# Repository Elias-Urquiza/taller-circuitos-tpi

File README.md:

# Proyecto Integrador del Taller de Circuitos Electrónicos

TP de tomi,nacho,elias y vero.

## 🐥 Git Branching: Guía Rápida con Panchito el Pollito 🐥

¡Hola, ameo! Soy Panchito, el pollito piola fui creado por IA para hacer más copado el usar Git 🐥, y te voy a guiar paso a paso para que aprendas cómo usar ramas (branches) en Git. Tranquilo, que lo hacemos simple y sin vueltas. ¡Vamo a meterle! 💪

---

## ¿Qué es una rama (branch)? 🌿

Bueno, imaginate que estás laburando en tu proyecto y querés probar algo nuevo sin que se rompa lo que ya tenés hecho. Ahí es donde entran las **ramas**. 🌱 Cada rama es como una copia separada del proyecto en la que podés hacer lío sin romper nada. Cuando ya esté todo pipí cucú, unís los cambios al proyecto principal y listo. 🎉

---

## Comandos Básicos para Trabajar con Ramas 🐾

### 1. Verificar en qué rama estás 🔍

Primero lo primero, ¿en qué rama estás? Para saberlo, usá este comando:

```bash
git branch
```

Te va a mostrar todas las ramas y te pone un asterisco `*` al lado de la que tenés activa. ¡Así sabés bien en qué andás! 💡

### 2. Crear una nueva rama 🌱

Cuando quieras hacer algo nuevo, lo mejor es crear una rama aparte (esto lo vamos a hacer todos una vez sola). Mandá este comando:

```bash
git branch pruebas_pepe
```

Este comando te crea la nueva rama, pero ¡ojo! todavía no te moviste a ella. Ahora vamos a eso. 🐥

### 3. Cambiar a una nueva rama 🎯

Para empezar a trabajar en la nueva rama, usá el siguiente comando:

```bash
git checkout pruebas_pepe
```

¡Listo! Ya estás en la nueva rama y podés hacer todos los cambios que quieras sin afectar el resto del proyecto. 🚀

### 4. Crear y cambiar a una nueva rama al mismo tiempo ⚡

Si te da fiaca hacer dos pasos, podés crear y cambiar a la nueva rama de una:

```bash
git checkout -b pruebas_pepe
```

Así no perdés tiempo y ya te ponés a laburar directo, como Panchito corriendo de acá para allá. 🐤

### 5. Verificar que estás en la nueva rama 🦅

Para asegurarte de que estás en la rama correcta, tirá de nuevo:

```bash
git branch
```

Ahí vas a ver el asterisco `*` al lado de la rama en la que estás. ¡Pío pío, ya estás listo para seguir! 🐥

### 6. Subir la nueva rama al repositorio remoto 🌍

Si querés compartir tus cambios con otros o simplemente guardar la rama en un repositorio remoto (como GitHub), tenés que hacer esto:

```bash
git push origin pruebas_pepe
```

Así, todo el mundo puede ver lo que hiciste y meter mano si hace falta. ¡No te olvides de esto cuando termines! 😉

### 7. Cambiar a una rama existente y subirla

1. **Cambiar a una rama existente:**
   ```bash
   git checkout nombre-de-la-rama
   ```

2. **Subir la rama al repositorio remoto si aún no está allí:**
   ```bash
   git push origin nombre-de-la-rama
   ```

### 8. Sincronizar una rama con `origin`

1. **Obtener los cambios del repositorio remoto:**
   ```bash
   git fetch origin
   ```

2. **Fusionar los cambios del repositorio remoto con tu rama local:**
   ```bash
   git merge origin/nombre-de-la-rama
   ```

   O, para actualizar tu rama local con los cambios remotos sin hacer un merge, puedes usar:
   ```bash
   git pull origin nombre-de-la-rama
   ```

### 9. Eliminar una rama en `origin`

1. **Eliminar una rama remota:**
   ```bash
   git push origin --delete nombre-de-la-rama
   ```

### 10. Ver ramas en `origin`

1. **Ver todas las ramas remotas:**
   ```bash
   git branch -r
   ```

2. **Ver todas las ramas locales y remotas:**
   ```bash
   git branch -a
   ```

### 11. Configurar el "upstream" de la rama

Si ves un mensaje que te indica que la rama no tiene un "upstream" configurado, usá este comando para empujar la rama y, al mismo tiempo, configurarla para que se conecte automáticamente con el repositorio remoto en futuras ocasiones:

```bash
git push --set-upstream origin nombre-de-la-rama
```

### ¿Qué hace este comando?

1. `git push`: Empuja los cambios al repositorio remoto.
2. `--set-upstream`: Configura la rama actual para que se conecte con la rama del mismo nombre en el repositorio remoto (en tu caso, `origin`).
3. `origin nombre-de-la-rama`: Le dice a Git que esta rama debe asociarse con la rama del mismo nombre en el repositorio remoto `origin`.

De ahora en más, cuando estés en la rama `nombre-de-la-rama`, podés usar simplemente `git push` sin tener que configurar el upstream de nuevo. ¡Listo!

---

## ¡Panchito dice: A practicar! 🐥🚀

Ahora que sabés cómo usar las ramas, ¡es hora de que te pongas a practicar! No tengas miedo de probar cosas nuevas. 
Git te cuida las espaldas, así que si algo no sale como esperabas, podés volver atrás sin problemas. ¡Vamos que se puede! 💪🐥🎉

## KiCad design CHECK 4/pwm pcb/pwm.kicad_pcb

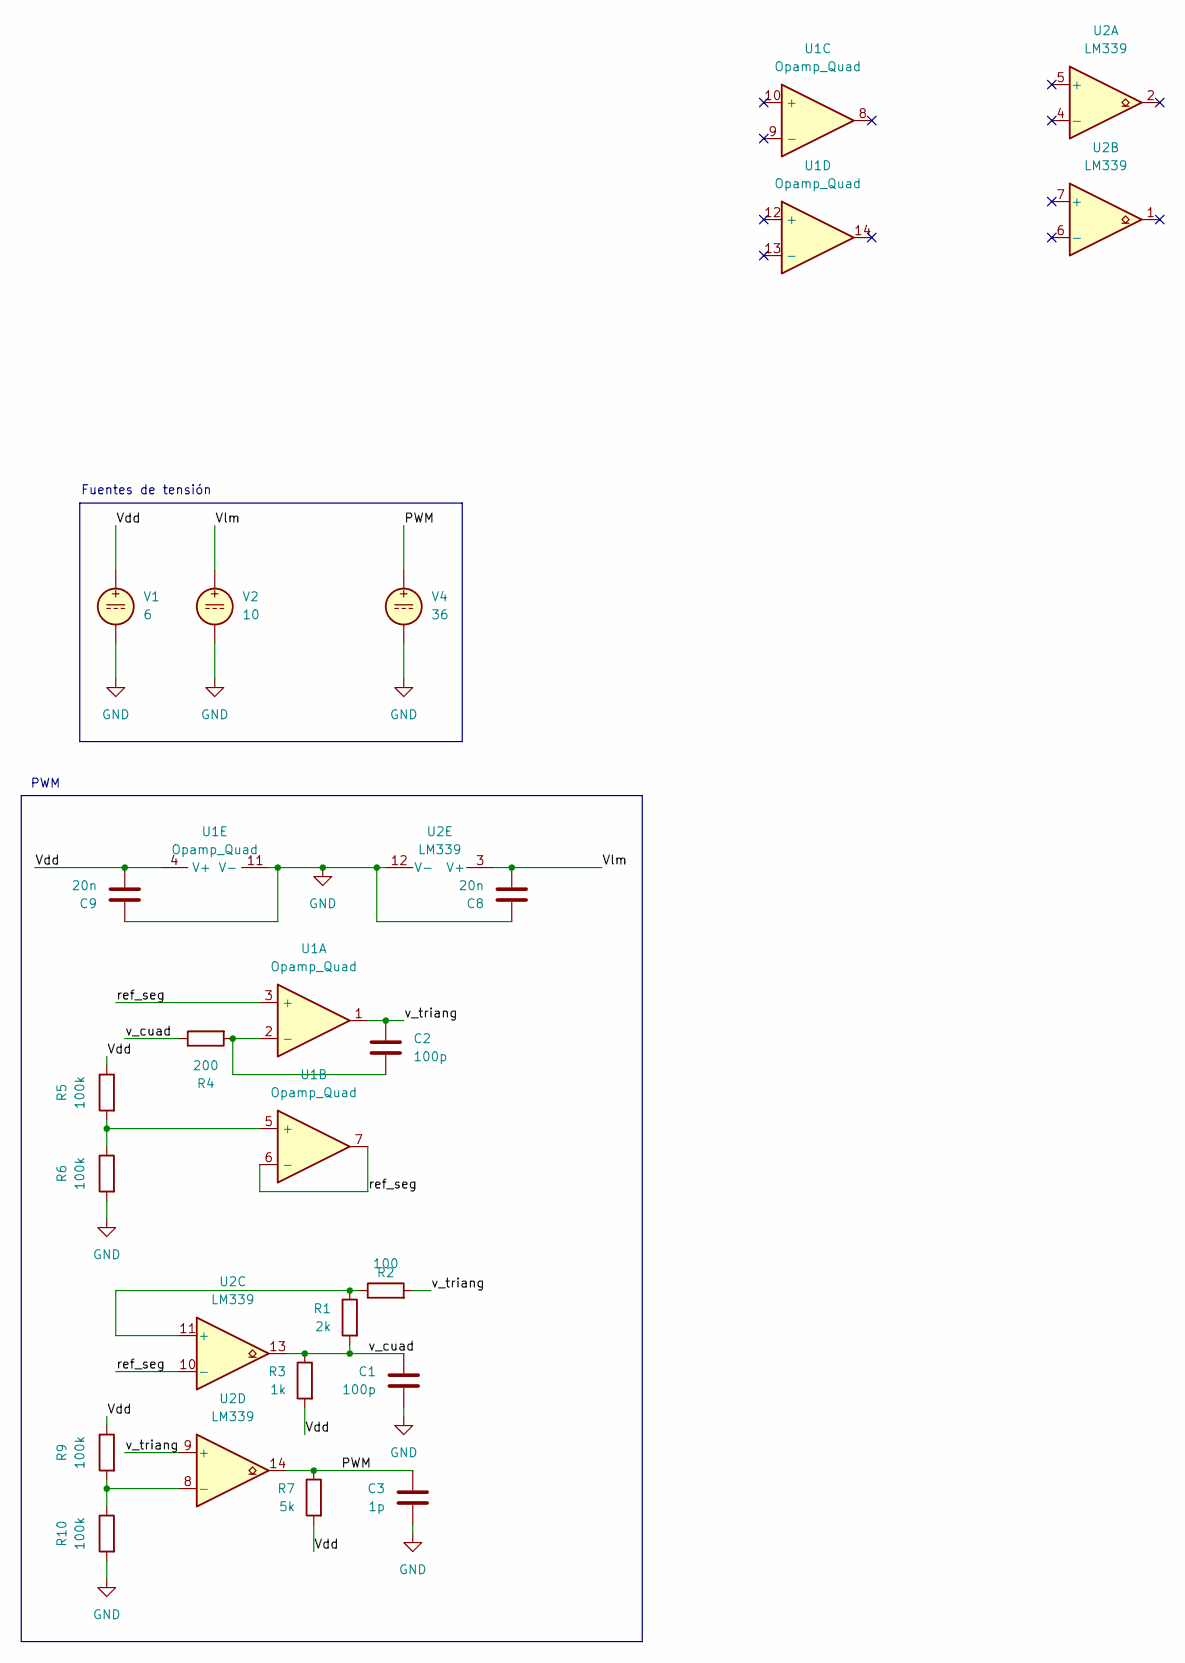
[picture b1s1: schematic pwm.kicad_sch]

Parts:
C1, C2: 100p; C_2225_5664Metric_Pad1.80x6.60mm_HandSolder
C3: 1p; C_2225_5664Metric_Pad1.80x6.60mm_HandSolder
C8, C9: 20n; C_2225_5664Metric_Pad1.80x6.60mm_HandSolder
R1: 2k; R_2512_6332Metric_Pad1.40x3.35mm_HandSolder
R2: 100; R_2512_6332Metric_Pad1.40x3.35mm_HandSolder
R3: 1k; R_2512_6332Metric_Pad1.40x3.35mm_HandSolder
R4: 200; R_2512_6332Metric_Pad1.40x3.35mm_HandSolder
R5, R6, R9, R10: 100k; R_2512_6332Metric_Pad1.40x3.35mm_HandSolder
R7: 5k; R_2512_6332Metric_Pad1.40x3.35mm_HandSolder
U1: Opamp_Quad; DIP-14_W10.16mm_LongPads
U2: LM339; DIP-14_W10.16mm_LongPads
V1: 6; PinHeader_2x01_P2.54mm_Vertical
V2: 10; PinHeader_2x01_P2.54mm_Vertical
V4: 36; PinHeader_2x01_P2.54mm_Vertical

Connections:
/PWM: C3.1, R7.1, U2.14, V4.1
/Vdd: C9.2, R3.2, R5.1, R7.2, R9.1, U1.4 (V+), V1.1
/Vlm: C8.2, U2.3 (V+), V2.1
/ref_seg: U1.3 (+), U1.6 (-), U1.7, U2.10 (-)
/v_cuad: C1.1, R1.2, R3.1, R4.1, U2.13
/v_triang: C2.1, R2.2, U1.1, U2.9 (+)
GND: C1.2, C3.2, C8.1, C9.1, R6.2, R10.2, U1.11 (V-), U2.12 (V-), V1.2, V2.2, V4.2
unnamed: C2.2, R4.2, U1.2 (-)
unnamed: R5.2, R6.1, U1.5 (+)
unnamed: R1.1, R2.1, U2.11 (+)
unnamed: R9.2, R10.1, U2.8 (-)

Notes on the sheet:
PWM
Fuentes de tensión

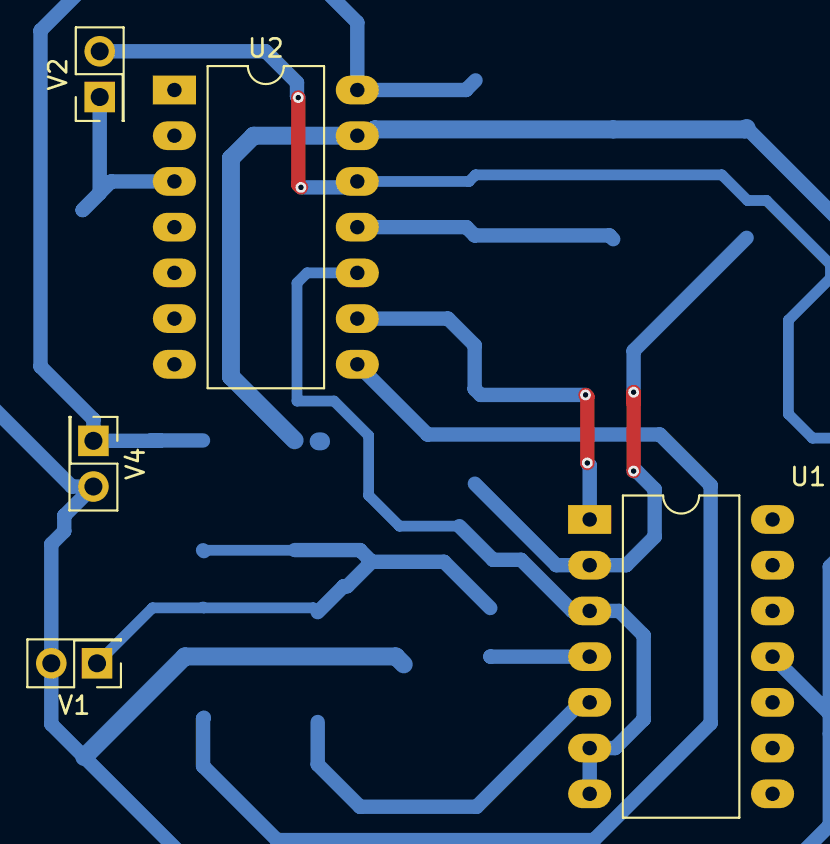
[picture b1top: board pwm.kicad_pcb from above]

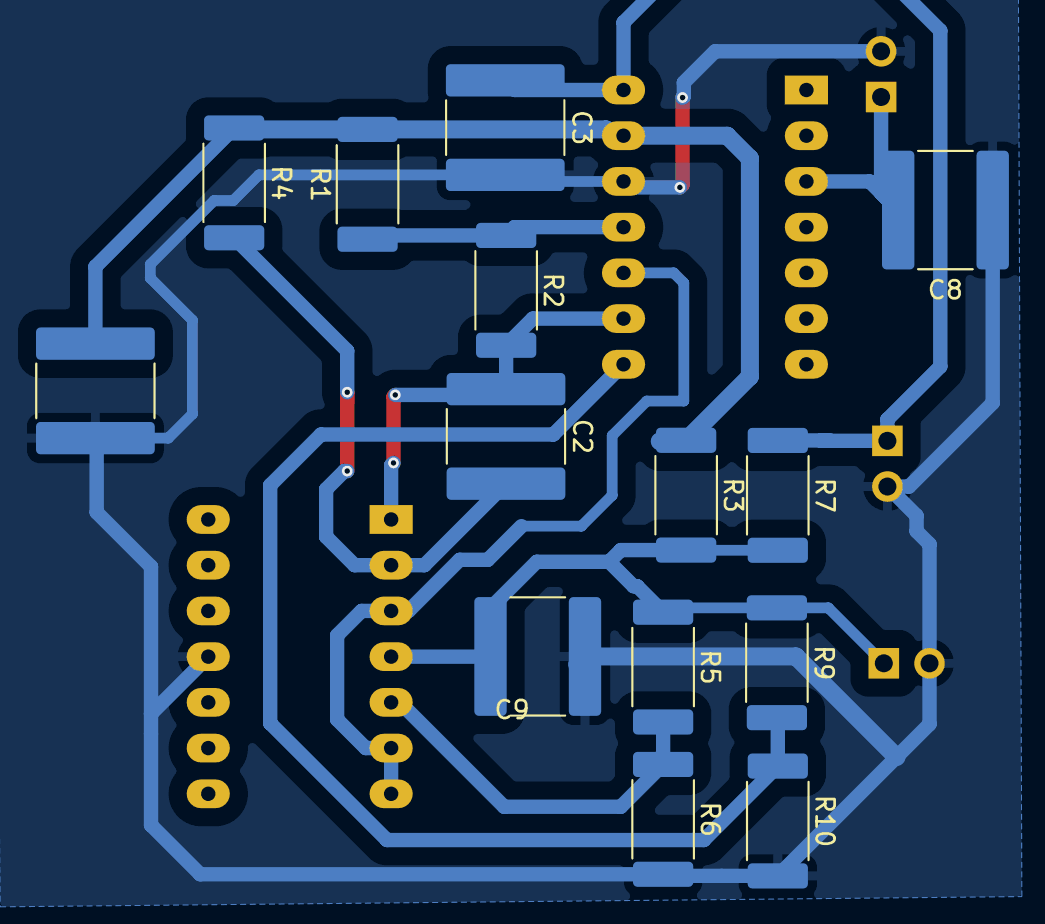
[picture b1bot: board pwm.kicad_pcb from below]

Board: 2 copper layers, 19 parts (14 on the bottom side), 11 nets.

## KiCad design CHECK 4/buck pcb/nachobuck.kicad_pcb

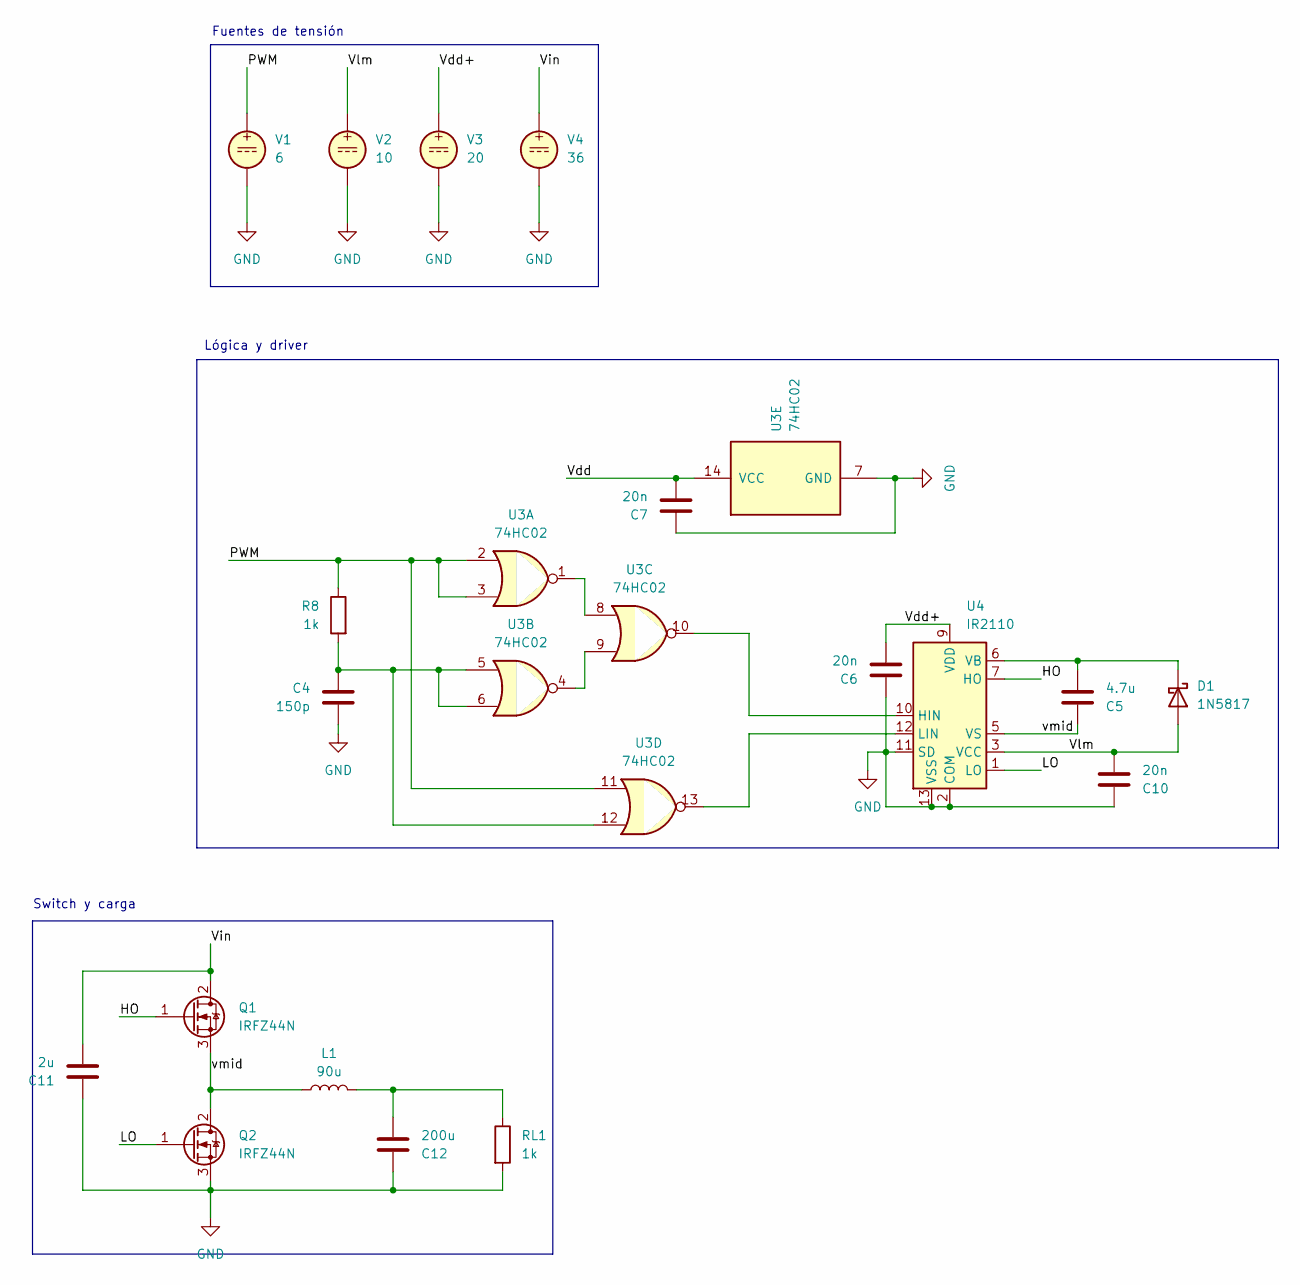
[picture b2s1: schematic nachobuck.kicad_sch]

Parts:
C4: 150p; C_2225_5664Metric_Pad1.80x6.60mm_HandSolder
C5: 4.7u; C_2225_5664Metric_Pad1.80x6.60mm_HandSolder
C6, C7, C10: 20n; C_2225_5664Metric_Pad1.80x6.60mm_HandSolder
C11: 2u; C_2225_5664Metric_Pad1.80x6.60mm_HandSolder
C12: 200u; C_2225_5664Metric_Pad1.80x6.60mm_HandSolder
D1: 1N5817; D_DO-41_SOD81_P10.16mm_Horizontal
L1: 90u; L_Axial_L30.0mm_D8.0mm_P35.56mm_Horizontal_Fastron_77A
Q1, Q2: IRFZ44N; TO-220-3_Vertical
R8: 1k; R_2512_6332Metric_Pad1.40x3.35mm_HandSolder
RL1: 1k; PinHeader_2x01_P2.54mm_Vertical
U3: 74HC02; DIP-14_W10.16mm_LongPads
U4: IR2110; DIP-14_W7.62mm
V1: 6; PinHeader_2x01_P2.54mm_Vertical
V2: 10; PinHeader_2x01_P2.54mm_Vertical
V3: 20; PinHeader_2x01_P2.54mm_Vertical
V4: 36; PinHeader_2x01_P2.54mm_Vertical

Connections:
/HO: Q1.1 (G), U4.7 (HO)
/LO: Q2.1 (G), U4.1 (LO)
/PWM: R8.1, U3.2, U3.3, U3.11, V1.1
/Vdd: C7.2, U3.14 (VCC)
/Vdd+: C6.2, U4.9 (VDD), V3.1
/Vin: C11.2, Q1.2 (D), V4.1
/Vlm: C10.2, D1.2 (A), U4.3 (VCC), V2.1
/vmid: C5.1, L1.1, Q1.3 (S), Q2.2 (D), U4.5 (VS)
GND: C4.2, C6.1, C7.1, C10.1, C11.1, C12.1, Q2.3 (S), RL1.2, U3.7 (GND), U4.2 (COM), U4.11 (SD), U4.13 (VSS), V1.2, V2.2, V3.2, V4.2
unnamed: C4.1, R8.2, U3.5, U3.6, U3.12
unnamed: C12.2, L1.2, RL1.1
unnamed: C5.2, D1.1 (K), U4.6 (VB)
unnamed: U3.1, U3.8
unnamed: U3.4, U3.9
unnamed: U3.10, U4.10 (HIN)
unnamed: U3.13, U4.12 (LIN)

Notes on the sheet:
Fuentes de tensión
Switch y carga
Lógica y driver

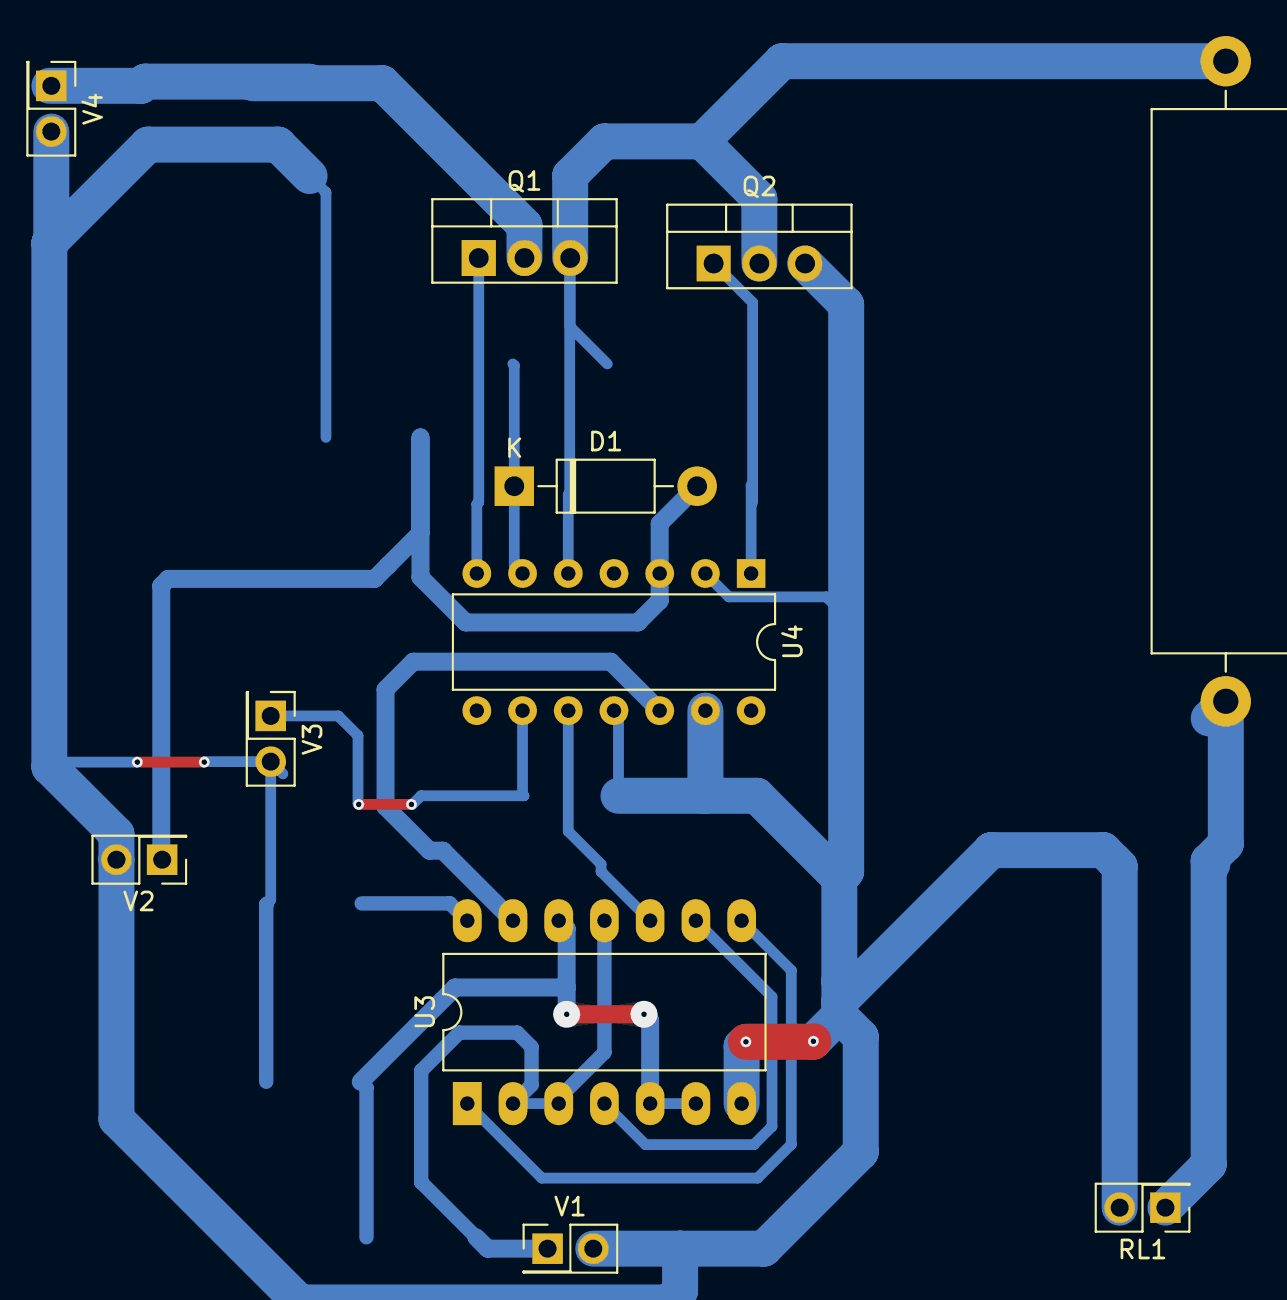
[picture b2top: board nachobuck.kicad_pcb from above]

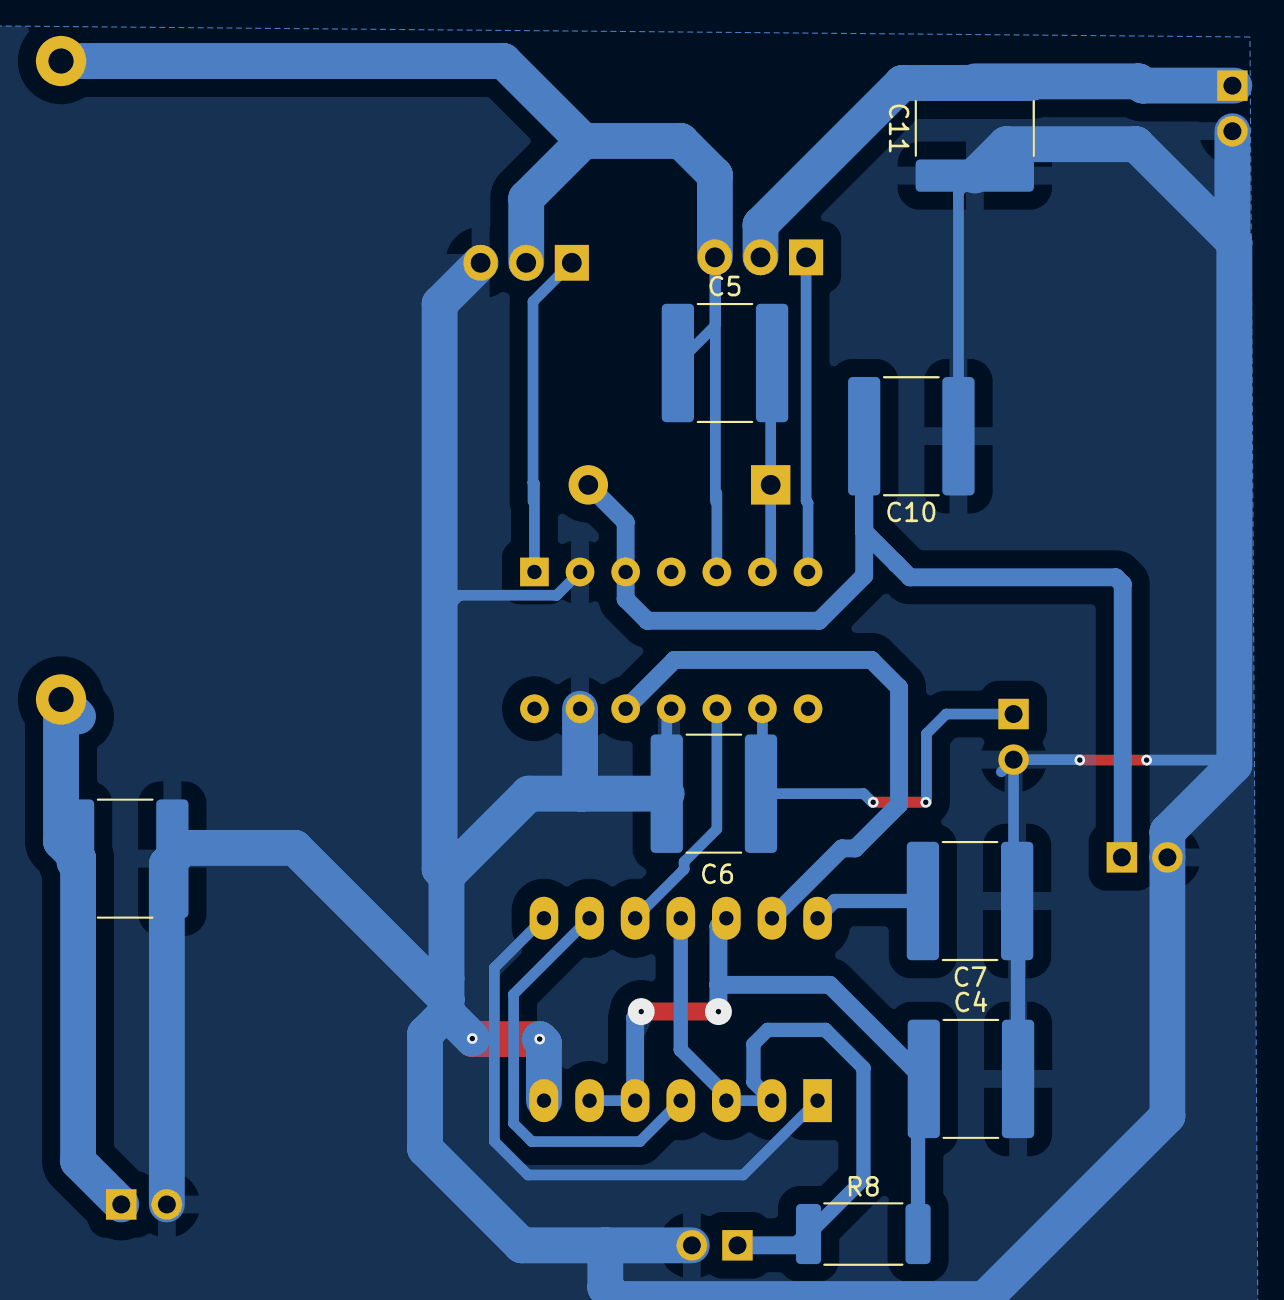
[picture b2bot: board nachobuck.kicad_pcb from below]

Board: 2 copper layers, 19 parts (8 on the bottom side), 16 nets.

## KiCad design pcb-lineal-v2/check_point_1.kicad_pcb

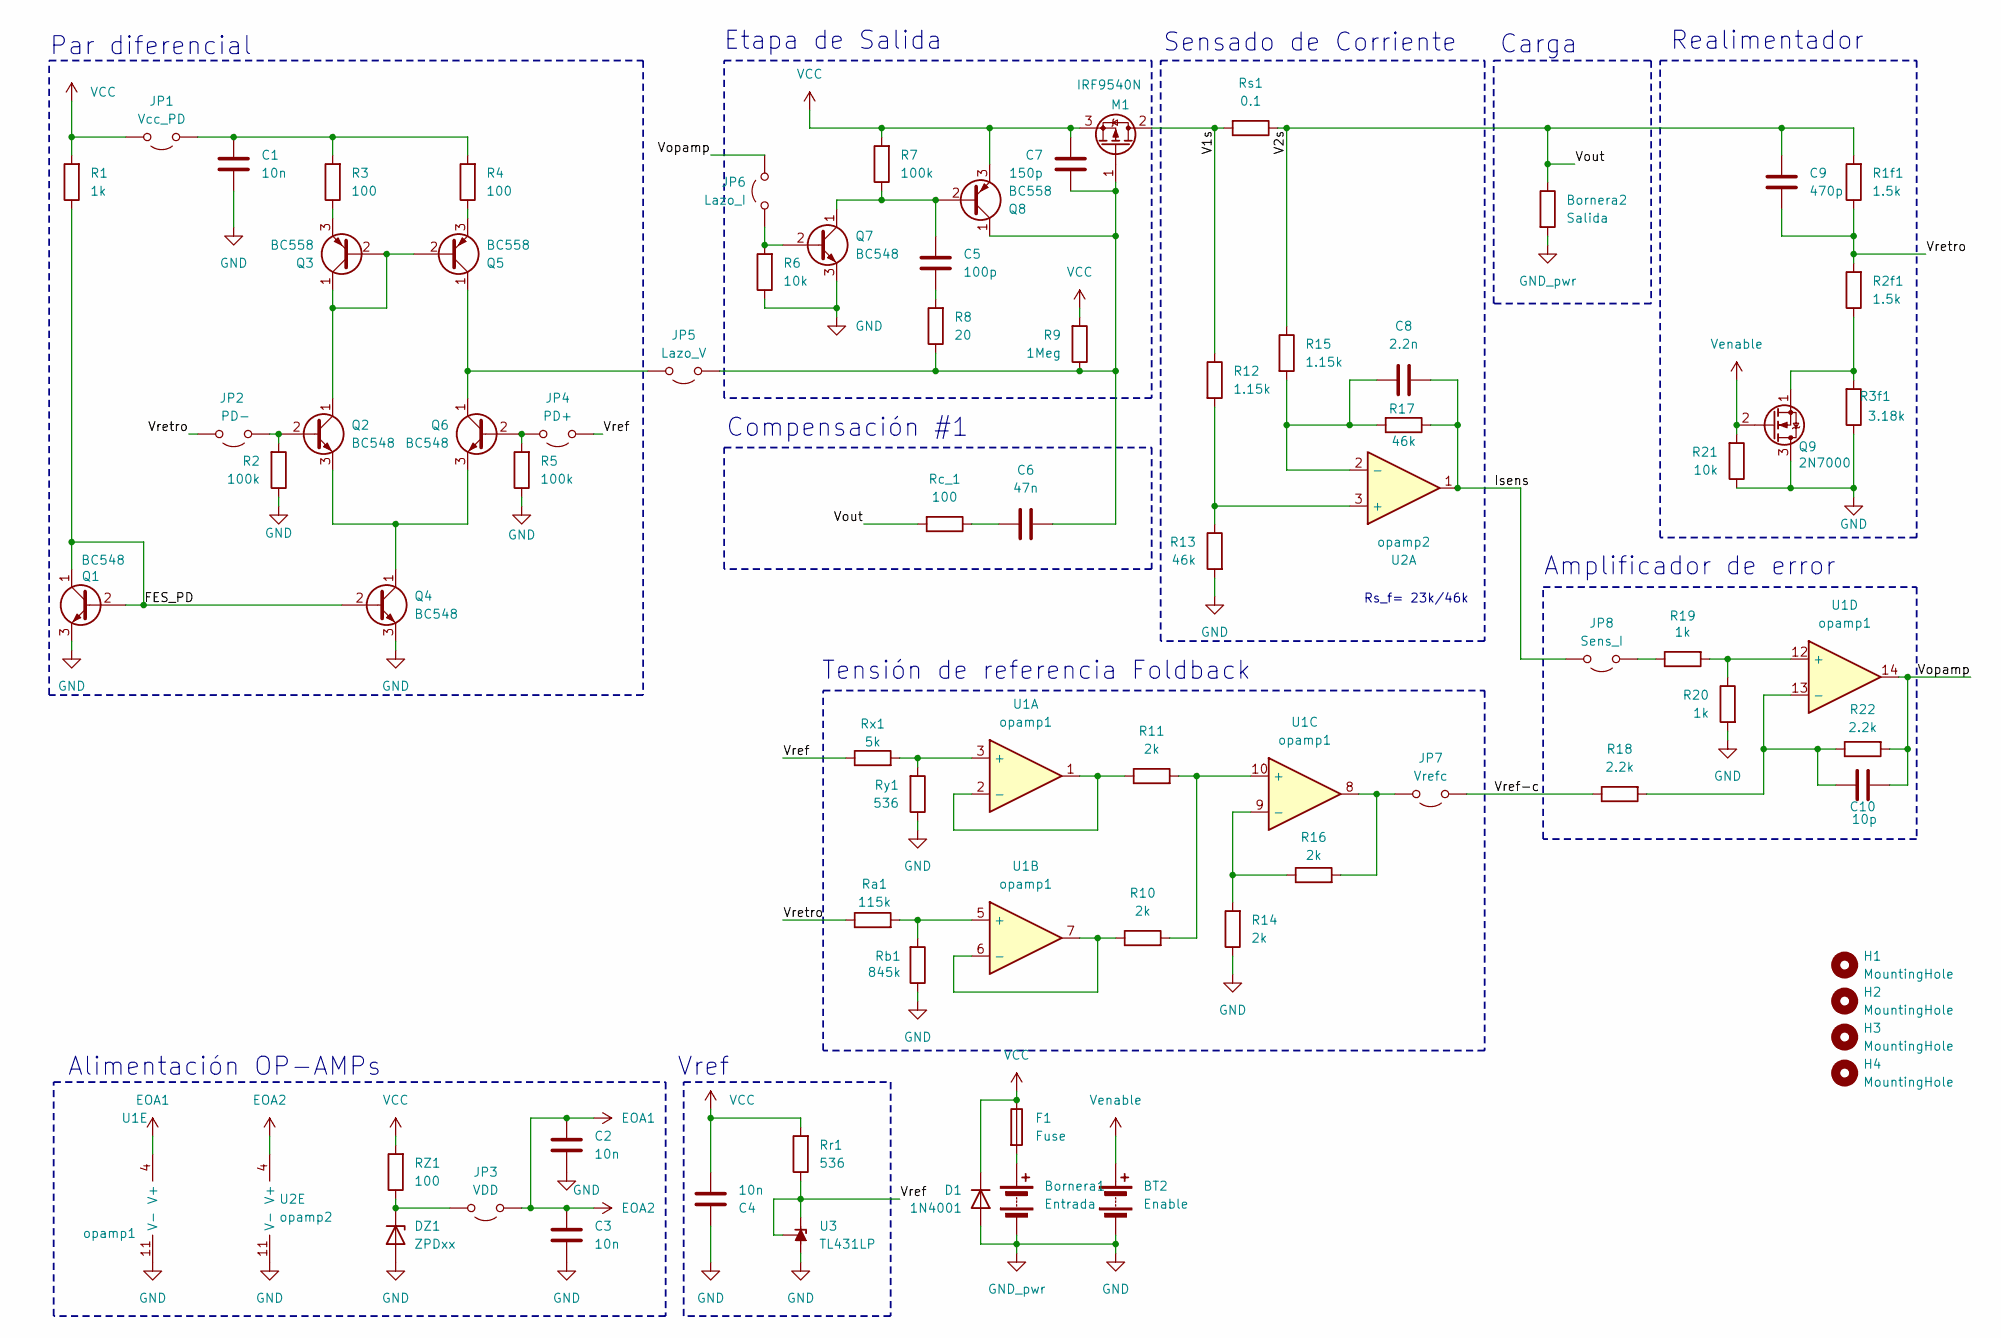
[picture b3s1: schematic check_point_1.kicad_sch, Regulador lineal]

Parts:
BT2: Enable; PinHeader_2x01_P2.54mm_Vertical
Bornera1: Entrada; bornera
Bornera2: Salida; bornera
C1, C2, C3, C4: 10n; C_Disc_D4.3mm_W1.9mm_P5.00mm
C5: 100p; C_Disc_D4.3mm_W1.9mm_P5.00mm
C6: 47n; C_Rect_L4.6mm_W3.0mm_P2.50mm_MKS02_FKP02
C7: 150p; C_Disc_D4.3mm_W1.9mm_P5.00mm
C8: 2.2n; C_Disc_D4.3mm_W1.9mm_P5.00mm
C9: 470p; C_Disc_D4.3mm_W1.9mm_P5.00mm
C10: 10p; C_Disc_D3.8mm_W2.6mm_P2.50mm
D1: 1N4001; D_DO-41_SOD81_P10.16mm_Horizontal
DZ1: ZPDxx; D_DO-35_SOD27_P10.16mm_Horizontal
F1: Fuse; R_1206_3216Metric_Pad1.30x1.75mm_HandSolder
H1, H2, H3, H4: MountingHole; MountingHole_2.1mm
JP1: Vcc_PD; PinHeader_1x02_P2.54mm_Vertical
JP2: PD-; PinHeader_1x02_P2.54mm_Vertical
JP3: VDD; PinHeader_1x02_P2.54mm_Vertical
JP4: PD+; PinHeader_1x02_P2.54mm_Vertical
JP5: Lazo_V; PinHeader_1x02_P2.54mm_Vertical
JP6: Lazo_I; PinHeader_1x02_P2.54mm_Vertical
JP7: Vrefc; PinHeader_1x02_P2.54mm_Vertical
JP8: Sens_I; PinHeader_1x02_P2.54mm_Vertical
M1: IRF9540N; TO-220-3_Vertical
Q1, Q2, Q4, Q6, Q7: BC548; TO-92_HandSolder
Q3, Q5, Q8: BC558; TO-92_HandSolder
Q9: 2N7000; TO-92_HandSolder
R1, R19, R20: 1k; R_Axial_DIN0207_L6.3mm_D2.5mm_P10.16mm_Horizontal
R1f1, R2f1: 1.5k; R_Axial_DIN0207_L6.3mm_D2.5mm_P10.16mm_Horizontal
R2, R5: 100k; R_Axial_DIN0207_L6.3mm_D2.5mm_P10.16mm_Horizontal
R3, R4: 100; R_Axial_DIN0207_L6.3mm_D2.5mm_P10.16mm_Horizontal
R3f1: 3.18k; R_Axial_DIN0207_L6.3mm_D2.5mm_P10.16mm_Horizontal
R6: 10k; R_Axial_DIN0207_L6.3mm_D2.5mm_P5.08mm_Vertical
R7: 100k; R_Axial_DIN0207_L6.3mm_D2.5mm_P5.08mm_Vertical
R8: 20; R_Axial_DIN0207_L6.3mm_D2.5mm_P5.08mm_Vertical
R9: 1Meg; R_Axial_DIN0207_L6.3mm_D2.5mm_P5.08mm_Vertical
R10, R11, R14, R16: 2k; R_Axial_DIN0207_L6.3mm_D2.5mm_P10.16mm_Horizontal
R12, R15: 1.15k; R_Axial_DIN0207_L6.3mm_D2.5mm_P10.16mm_Horizontal
R13, R17: 46k; R_Axial_DIN0207_L6.3mm_D2.5mm_P10.16mm_Horizontal
R18: 2.2k; R_Axial_DIN0207_L6.3mm_D2.5mm_P5.08mm_Vertical
R21: 10k; R_Axial_DIN0207_L6.3mm_D2.5mm_P10.16mm_Horizontal
R22: 2.2k; R_Axial_DIN0207_L6.3mm_D2.5mm_P10.16mm_Horizontal
RZ1: 100; R_Axial_DIN0207_L6.3mm_D2.5mm_P10.16mm_Horizontal
Ra1: 115k; R_Axial_DIN0207_L6.3mm_D2.5mm_P10.16mm_Horizontal
Rb1: 845k; R_Axial_DIN0207_L6.3mm_D2.5mm_P10.16mm_Horizontal
Rc_1: 100; R_Axial_DIN0207_L6.3mm_D2.5mm_P10.16mm_Horizontal
Rr1: 536; R_Axial_DIN0207_L6.3mm_D2.5mm_P10.16mm_Horizontal
Rs1: 0.1; R_Axial_DIN0918_L18.0mm_D9.0mm_P25.40mm_Horizontal
Rx1: 5k; R_Axial_DIN0207_L6.3mm_D2.5mm_P10.16mm_Horizontal
Ry1: 536; R_Axial_DIN0207_L6.3mm_D2.5mm_P10.16mm_Horizontal
U1: opamp1; DIP-14_W7.62mm_Socket
U2: opamp2; DIP-14_W7.62mm_Socket
U3: TL431LP; TO-92_HandSolder

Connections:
/FES_PD: Q1.1 (C), Q1.2 (B), Q4.2 (B), R1.1
/Isens: C8.2, JP8.2 (B), R17.1, U2.1
/V1s: M1.2 (D), R12.1, Rs1.2
/V2s: Bornera2.1, C9.1, R1f1.2, R15.1, Rc_1.2, Rs1.1
/Vopamp: C10.1, JP6.2 (B), R22.2, U1.14
/Vref: JP4.2 (B), Rr1.1, Rx1.1, U3.1 (REF), U3.3 (K)
/Vref-c: JP7.2 (B), R18.1
/Vretro: C9.2, JP2.2 (B), R1f1.1, R2f1.2, Ra1.1
EOA1: C2.1, C3.1, JP3.2 (B), U1.4 (V+), U2.4 (V+)
GND: BT2.2 (-), Bornera1.2 (-), Bornera2.2, C1.2, C2.2, C3.2, C4.1, D1.2 (A), DZ1.2 (A), Q1.3 (E), Q4.3 (E), Q7.3 (E), Q9.3 (D), R2.1, R3f1.1, R5.1, R6.1, R13.2, R14.1, R20.2, R21.1, Rb1.1, Ry1.1, U1.11 (V-), U2.11 (V-), U3.2 (A)
unnamed: Bornera1.1 (+), F1.2
unnamed: C5.2, R8.2
unnamed: C6.1, Rc_1.1
unnamed: DZ1.1 (K), JP3.1 (A), RZ1.1
unnamed: C1.1, JP1.2 (B), R3.2, R4.2
unnamed: JP2.1 (A), Q2.2 (B), R2.2
unnamed: JP4.1 (A), Q6.2 (B), R5.2
unnamed: JP5.1 (A), Q5.1 (C), Q6.1 (C)
unnamed: C6.2, C7.2, JP5.2 (B), M1.1 (G), Q8.1 (C), R8.1, R9.1
unnamed: JP6.1 (A), Q7.2 (B), R6.2
unnamed: JP7.1 (A), R16.2, U1.8
unnamed: JP8.1 (A), R19.1
unnamed: Q2.1 (C), Q3.1 (C), Q3.2 (B), Q5.2 (B)
unnamed: Q2.3 (E), Q4.1 (C), Q6.3 (E)
unnamed: Q3.3 (E), R3.1
unnamed: Q5.3 (E), R4.1
unnamed: C5.1, Q7.1 (C), Q8.2 (B), R7.1
unnamed: Q9.1 (S), R2f1.1, R3f1.2
unnamed: Rx1.2, Ry1.2, U1.3 (+)
unnamed: R11.1, U1.1, U1.2 (-)
unnamed: Ra1.2, Rb1.2, U1.5 (+)
unnamed: R10.1, U1.6 (-), U1.7
unnamed: R10.2, R11.2, U1.10 (+)
unnamed: R14.2, R16.1, U1.9 (-)
unnamed: R19.2, R20.1, U1.12 (+)
unnamed: C10.2, R18.2, R22.1, U1.13 (-)
unnamed: R12.2, R13.1, U2.3 (+)
unnamed: C8.1, R15.2, R17.2, U2.2 (-)
VCC: C4.2, C7.1, D1.1 (K), F1.1, JP1.1 (A), M1.3 (S), Q8.3 (E), R1.2, R7.2, R9.2, RZ1.2, Rr1.2
Venable: BT2.1 (+), Q9.2 (G), R21.2

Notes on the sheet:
Par diferencial
Realimentador
Etapa de Salida
Vref
Carga
Amplificador de error
Sensado de Corriente
Alimentación OP-AMPs
Tensión de referencia Foldback
Rs_f= 23k/46k
Compensación #1

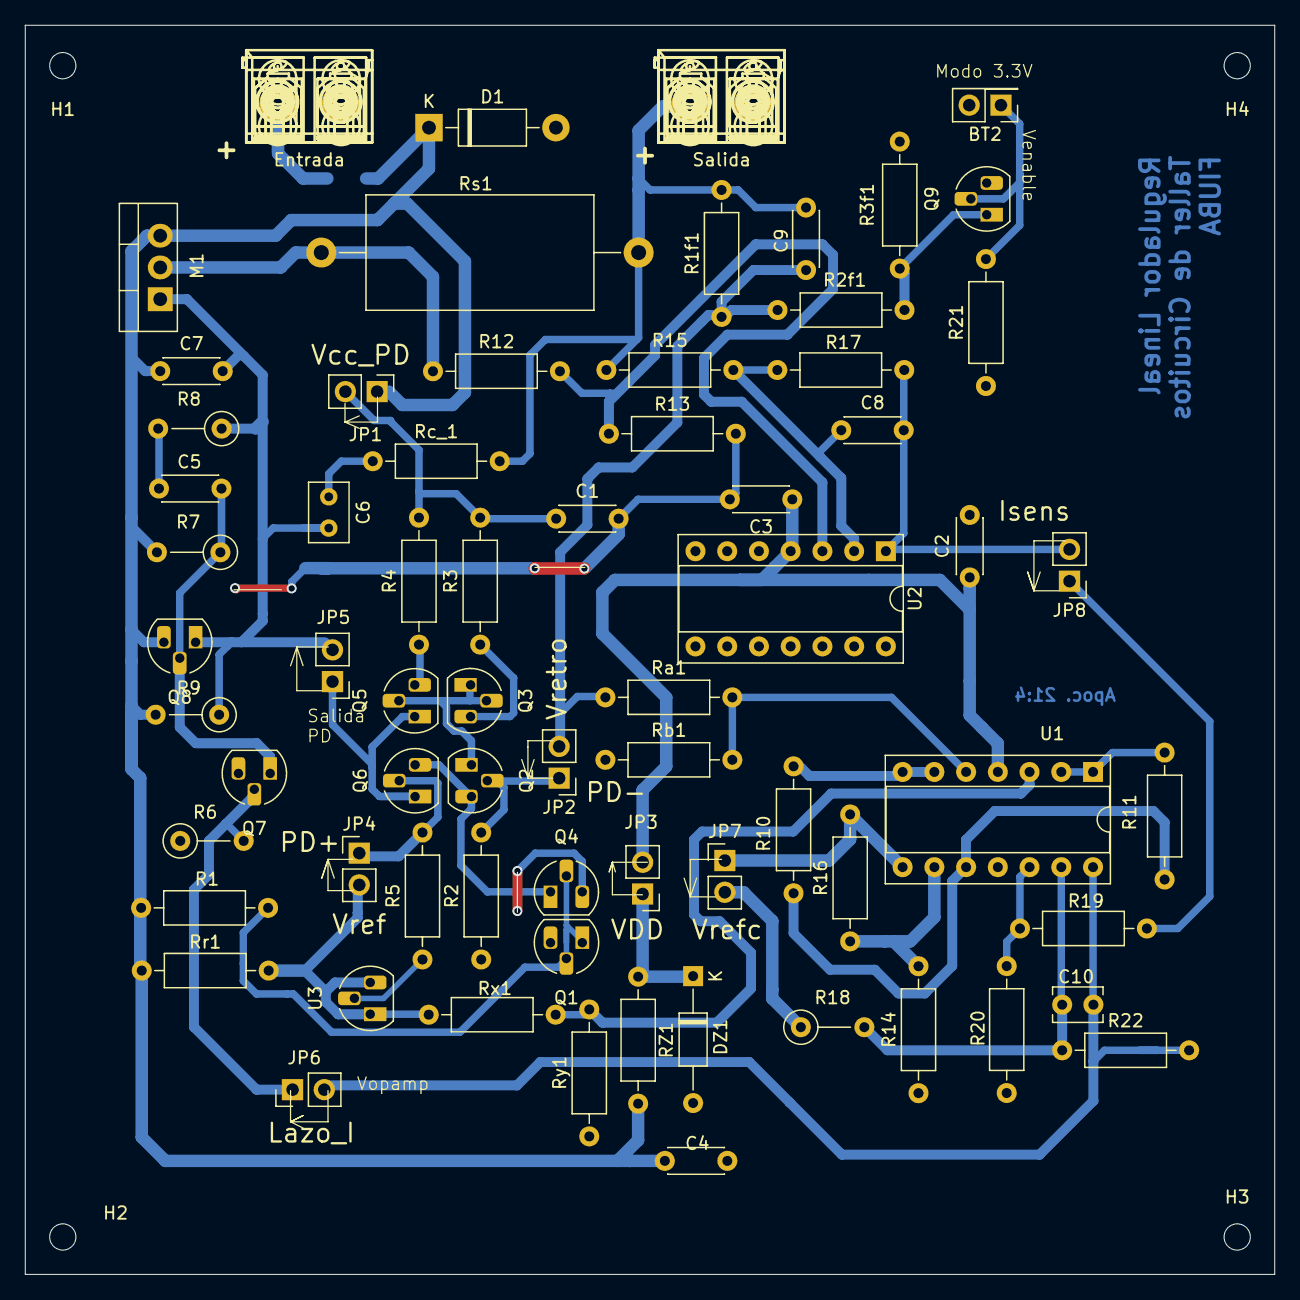
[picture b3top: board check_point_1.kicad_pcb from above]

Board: 2 copper layers, 100.0 x 100.0 mm, 74 parts (1 on the bottom side), 40 nets.

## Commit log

2024-09-19 Added README.md
2024-09-19 organizando carpetitas
2024-09-19 mas cosas que tenemos
2024-09-19 organizandonos
2024-09-19 completar con lso que faltan
2024-09-19 como usar git
2024-09-19 guia git
2024-09-19 panchito
2024-09-22 Clase Pre-Check02
    Hay que revisar la curva de foldback. Si sigue funcionando es que es estable.
    Para compensar lo hacemos en el lazo de corriente donde tenemos las resistencias Rx,Ry, o Ra,Rb
    Revisar que las fuentes esten bien
2024-09-23 lazo de tension compensado. se agrega un adelanto de fase con c1 de 1.2n, cero en 100k y se amplia el margen de fase con c3 de 2.2n a aprox 70 grados
2024-09-23 lazo de tension ajustes finos. lazo de corriente problemitas
2024-09-23 vemos que si cambiamos los capacitores mejora el margen de fase
2024-09-25 Lazo Corriente Pt 2
    Intento de compensar lazo de corriente - Dejar en 6.66666 Ohm la RL
2024-09-27 archivos del lazo de corriente, revisar rta en frecuencia que hay algo raro, calculo que falta desconectar vopamp
2024-09-27 todo hasta hhyp
2024-09-28 Clase del Check02
    Debemos terminar el híbrido
2024-09-28 Agregados circuitos IT_WORKS
2024-09-28 Me falto un archivo .net
2024-09-28 remplazar C3 a 33p mejora el BW y la rta escalon
2024-09-29 laburo del 28, tomi y elias cambian capacitor, pruebas agregadaas muchas, mide fase etc
2024-09-29 Ultimo push a este
2024-09-30 Versiones Finales Tension
2024-09-30 nuevo valor del capacitor NO TOCAR ASI ANDA
2024-10-01 sacando toda la basura y dejando lo posta
2024-10-23 todo lo nuevo
2024-10-28 lo ultimo
2024-11-05 Agrego primeras simus de check4
2024-11-05 Revert "Agrego primeras simus de check4"
    This reverts commit 095fad8e8bc92e7dd69fa426879e592138059da8.
2024-11-05 Agrego Simus iniciales del Check 4
2024-11-05 Agrego circuito del gate driver
2024-11-07 cosas del check 3 viejas
2024-11-08 docs del disenio del toroide
2024-11-10 pcbs
2024-11-10 cambios check04
2024-11-12 switching library
    fightin'
2024-12-02 check 05
    ver check 04
